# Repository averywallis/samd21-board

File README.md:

# samd21-board
 KiCad files for a SAMD21 dev board

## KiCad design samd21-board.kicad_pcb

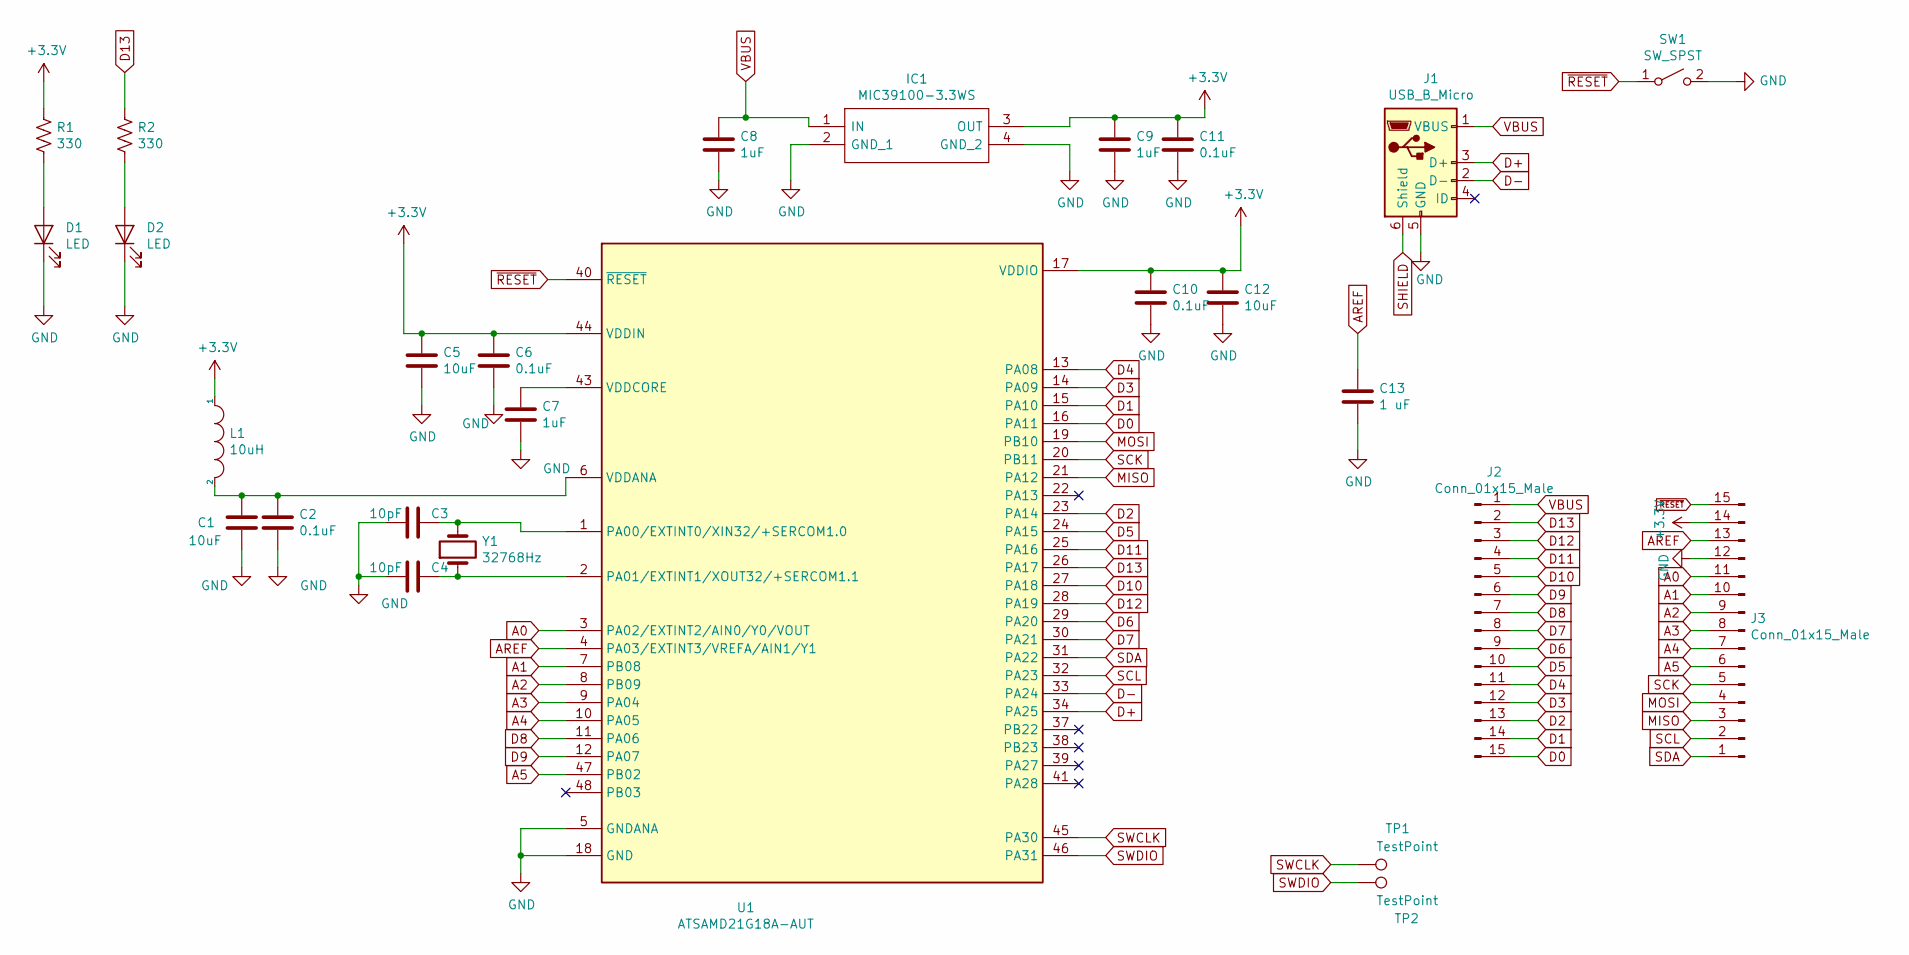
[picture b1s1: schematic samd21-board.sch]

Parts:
C1, C5, C12: 10uF; C_0805_2012Metric_Pad1.15x1.40mm_HandSolder; MPN TMK212BBJ106KG-T
C2: 0.1uF; C_0805_2012Metric_Pad1.15x1.40mm_HandSolder
C3, C4: 10pF; C_0805_2012Metric_Pad1.15x1.40mm_HandSolder; MPN CL21C100JBANNNC
C6, C10, C11: 0.1uF; C_0805_2012Metric_Pad1.15x1.40mm_HandSolder; MPN CL21B104KACNNNC
C7, C8, C9: 1uF; C_0805_2012Metric_Pad1.15x1.40mm_HandSolder; MPN CL21B105KAFNNNE
C13: 1 uF; C_0805_2012Metric_Pad1.15x1.40mm_HandSolder; MPN CL21B105KAFNNNE
D1, D2: LED; D_0805_2012Metric_Pad1.15x1.40mm_HandSolder; MPN LTST-C171KRKT
IC1: MIC39100-3.3WS; SOT230P700X180-4N; MPN MIC39100-3.3WS
J1: USB_B_Micro; USB_Micro-B_Molex_47346-0001; MPN 47346-0001
J2: Conn_01x15_Male; PinHeader_1x15_P2.54mm_Vertical; MPN 68000-416HLF
J3: Conn_01x15_Male; PinHeader_1x15_P2.54mm_Vertical
L1: 10uH; L_0805_2012Metric_Pad1.15x1.40mm_HandSolder; MPN CB2012T100KR
R1, R2: 330; R_0805_2012Metric_Pad1.15x1.40mm_HandSolder; MPN ERJ-P06J331V
SW1: SW_SPST; SW_SPST_B3S-1000; MPN B3S-1000
TP1, TP2: TestPoint; TestPoint_Pad_D2.0mm
U1: ATSAMD21G18A-AUT; TQFP-48_7x7mm_P0.5mm_hand_solder; MPN ATSAMD21G18A-AUT
Y1: 32768Hz; ABS-07; MPN ABS07-32.768KHZ-7-T

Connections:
+3V3: C5.1, C6.1, C9.1, C10.1, C11.1, C12.1, IC1.3 (OUT), J3.14, L1.1, R1.1, U1.17 (VDDIO), U1.36 (VDDIO), U1.44 (VDDIN)
A0: J3.11, U1.3 (PA02/EXTINT2/AIN0/Y0/VOUT)
A1: J3.10, U1.7 (PB08)
A2: J3.9, U1.8 (PB09)
A3: J3.8, U1.9 (PA04)
A4: J3.7, U1.10 (PA05)
A5: J3.6, U1.47 (PB02)
AREF: C13.1, J3.13, U1.4 (PA03/EXTINT3/VREFA/AIN1/Y1)
D0: J2.15, U1.16 (PA11)
D1: J2.14, U1.15 (PA10)
D2: J2.13, U1.23 (PA14)
D3: J2.12, U1.14 (PA09)
D4: J2.11, U1.13 (PA08)
D5: J2.10, U1.24 (PA15)
D6: J2.9, U1.29 (PA20)
D7: J2.8, U1.30 (PA21)
D8: J2.7, U1.11 (PA06)
D9: J2.6, U1.12 (PA07)
D10: J2.5, U1.27 (PA18)
D11: J2.4, U1.25 (PA16)
D12: J2.3, U1.28 (PA19)
D13: J2.2, R2.1, U1.26 (PA17)
D+: J1.3 (D+), U1.34 (PA25)
D-: J1.2 (D-), U1.33 (PA24)
GND: C1.2, C2.2, C3.2, C4.2, C5.2, C6.2, C7.2, C8.2, C9.2, C10.2, C11.2, C12.2, C13.2, D1.1 (K), D2.1 (K), IC1.2 (GND_1), IC1.4 (GND_2), J1.5 (GND), J3.12, SW1.2 (B), U1.5 (GNDANA), U1.18 (GND), U1.35 (GND), U1.42 (GND)
MISO: J3.3, U1.21 (PA12)
MOSI: J3.4, U1.19 (PB10)
unnamed: C1.1, C2.1, L1.2, U1.6 (VDDANA)
unnamed: C3.1, U1.1 (PA00/EXTINT0/XIN32/+SERCOM1.0), Y1.2
unnamed: C4.1, U1.2 (PA01/EXTINT1/XOUT32/+SERCOM1.1), Y1.1
unnamed: C7.1, U1.43 (VDDCORE)
unnamed: D1.2 (A), R1.2
unnamed: D2.2 (A), R2.2
SCK: J3.5, U1.20 (PB11)
SCL: J3.2, U1.32 (PA23)
SDA: J3.1, U1.31 (PA22)
SHIELD: J1.6 (Shield)
SWCLK: TP1.1, U1.45 (PA30)
SWDIO: TP2.1, U1.46 (PA31)
VBUS: C8.1, IC1.1 (IN), J1.1 (VBUS), J2.1
~RESET: J3.15, SW1.1 (A), U1.40 (~RESET)

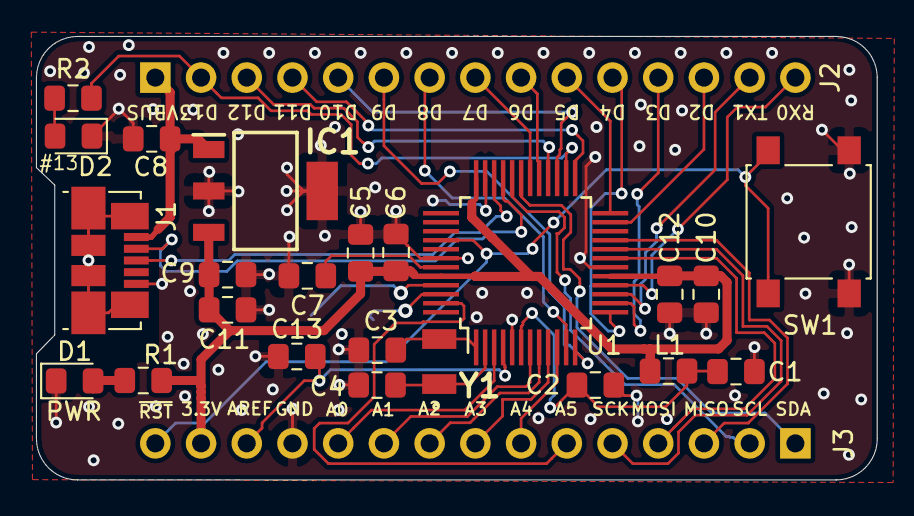
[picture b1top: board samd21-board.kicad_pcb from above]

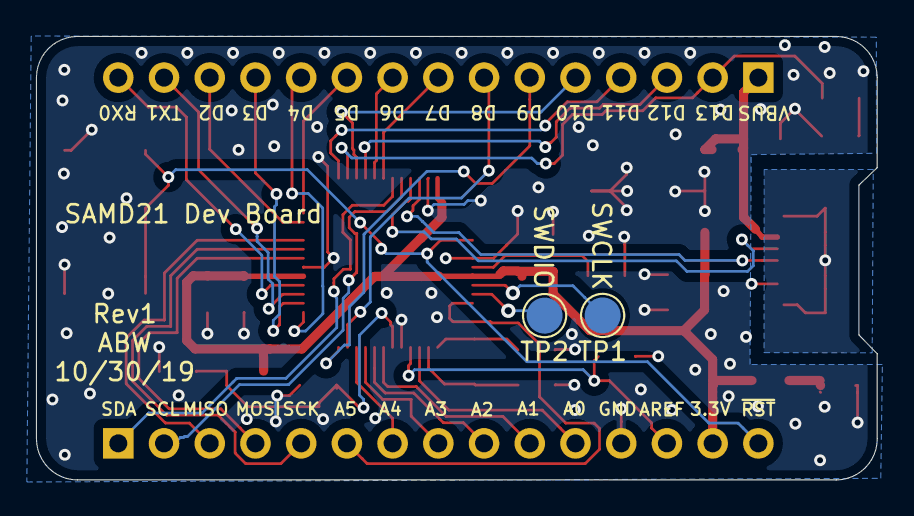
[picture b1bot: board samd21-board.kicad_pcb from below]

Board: 2 copper layers, 46.7 x 24.6 mm, 27 parts (2 on the bottom side), 40 nets.

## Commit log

2020-01-08 Photos added
    Added some images of Rev1, since I finally was able to assemble it!
2020-01-15 added some positional files for components
2020-02-26 Update fp-info-cache
2022-01-29 Create LICENSE
